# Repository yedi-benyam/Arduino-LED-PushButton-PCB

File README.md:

# Arduino LED & Push Button PCB

## Overview
This project is a simple Arduino Nano PCB designed in KiCad. It demonstrates basic PCB design practices, including schematic capture, component placement, routing, and design rule checking.

## Components
- Arduino Nano
- Push Button
- LED
- 220 Ω Resistor
- 10 kΩ Resistor

## Features
- Push button input
- LED output
- Compact single-layer PCB
- Designed using KiCad 10

## Author
Yedi Benyam

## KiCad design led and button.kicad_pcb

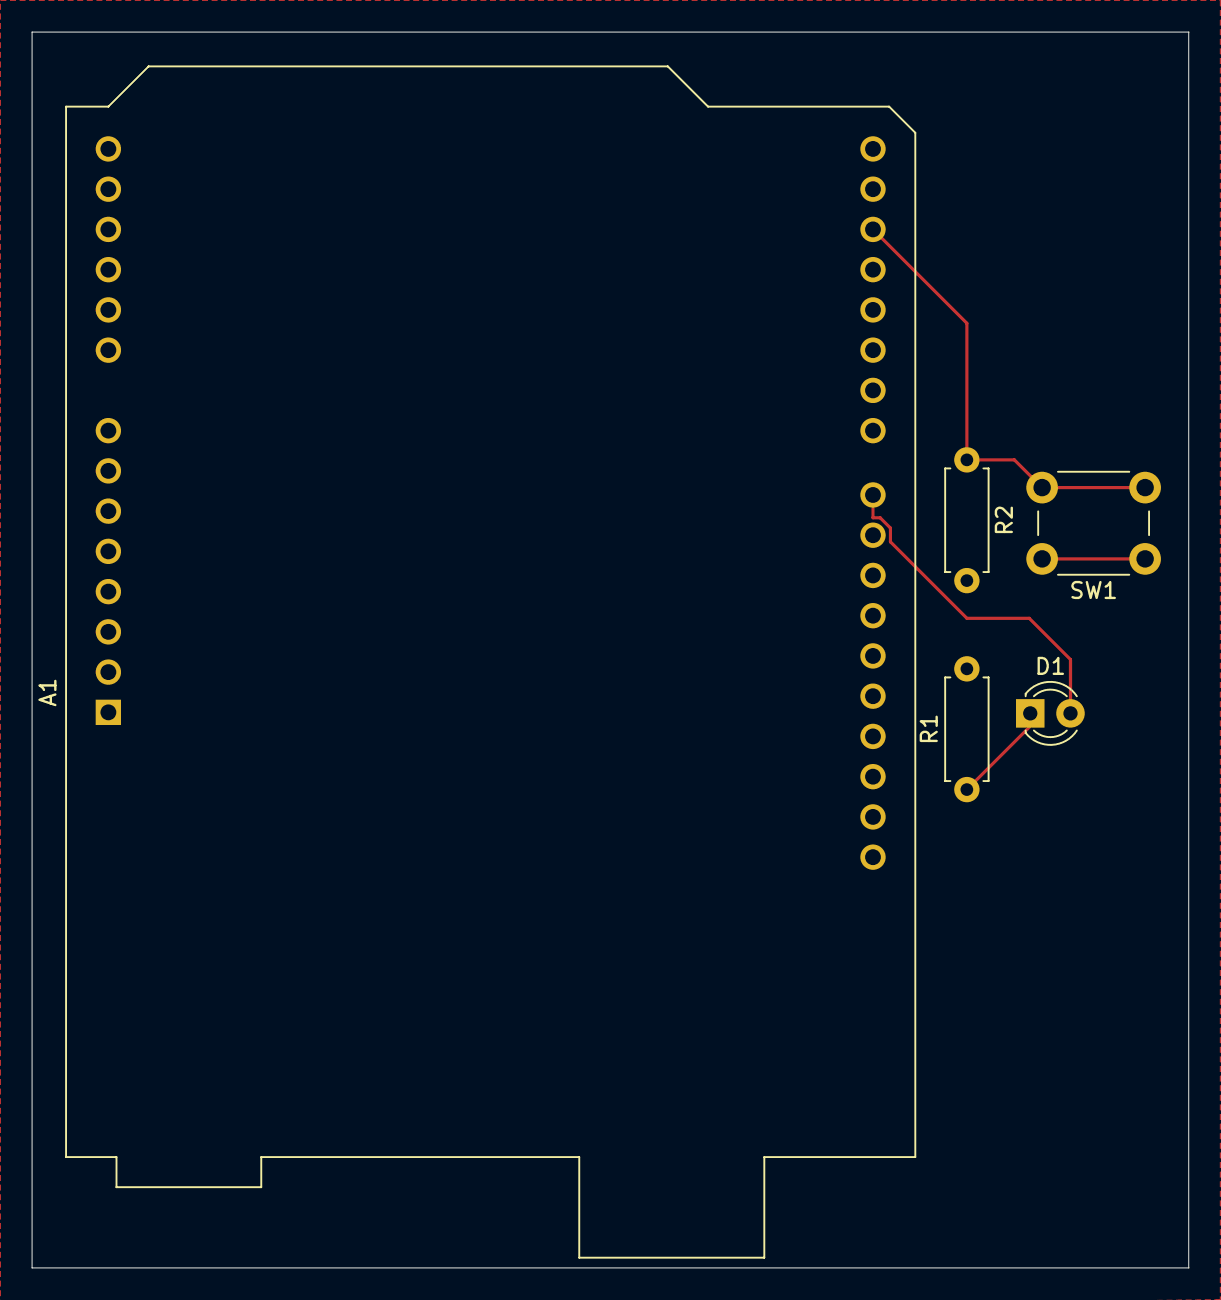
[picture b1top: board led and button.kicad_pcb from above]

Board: 2 copper layers, 73.0 x 78.0 mm, 5 parts (0 on the bottom side), 4 nets.

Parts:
A1: Arduino_UNO_R3
D1: LED; LED_D3.0mm
R1: 220; R_Axial_DIN0207_L6.3mm_D2.5mm_P7.62mm_Horizontal
R2: 10K; R_Axial_DIN0207_L6.3mm_D2.5mm_P7.62mm_Horizontal
SW1: SW_Push; SW_PUSH_6mm

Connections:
GND: R1.2, R2.2
unnamed: A1.17 (D2), R2.1, SW1.2
unnamed: A1.23 (D8), D1.2 (A)
unnamed: D1.1 (K), R1.1
